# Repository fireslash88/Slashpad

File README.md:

## Slashpad

This is my submission for the Hackpad challenge!

Slashpad is a 6 key macropad with a Rotary Encoder and OLED Display, and uses the QMK Firmware!

--- 
### Inspiration for the name of the pad

I named the pad after my username online! As you can see, my name on github is "fireslash88" and that's pretty much the same for every other account I have online!
I have another username that I actually use more than this one but I prefer to use slash now..

---
### BOM
- 1x Seeed XIAO RP2040
- 6x Cherry MX Switches
- 6x Keycaps
- 1x EC11 Rotary Encoder
- 1x 0.91 inch OLED display
- 7x through-hole 1N4148 Diodes
- 4x M3x16mm screws
- 1x 3D Printed Case
---
### PCB
This is the PCB I created for the Multipad!

This is the schematic that I created using KiCad 10.0!

This is the PCB!

---
### Case
This is the case I modeled in Fusion 360!

---
### Firmware

The Slashpad uses the QMK firmware for everything!
(Will include VIA in the future) 

---
### Thanks!

A great thanks to Hack Club to have made this project possible!

---

### Cats
Yes. I love cats so I decided to put some silly cats I found on Pinterest on the PCB. They're pretty and I love them so uhh... Yeah... Cats.. Meow..

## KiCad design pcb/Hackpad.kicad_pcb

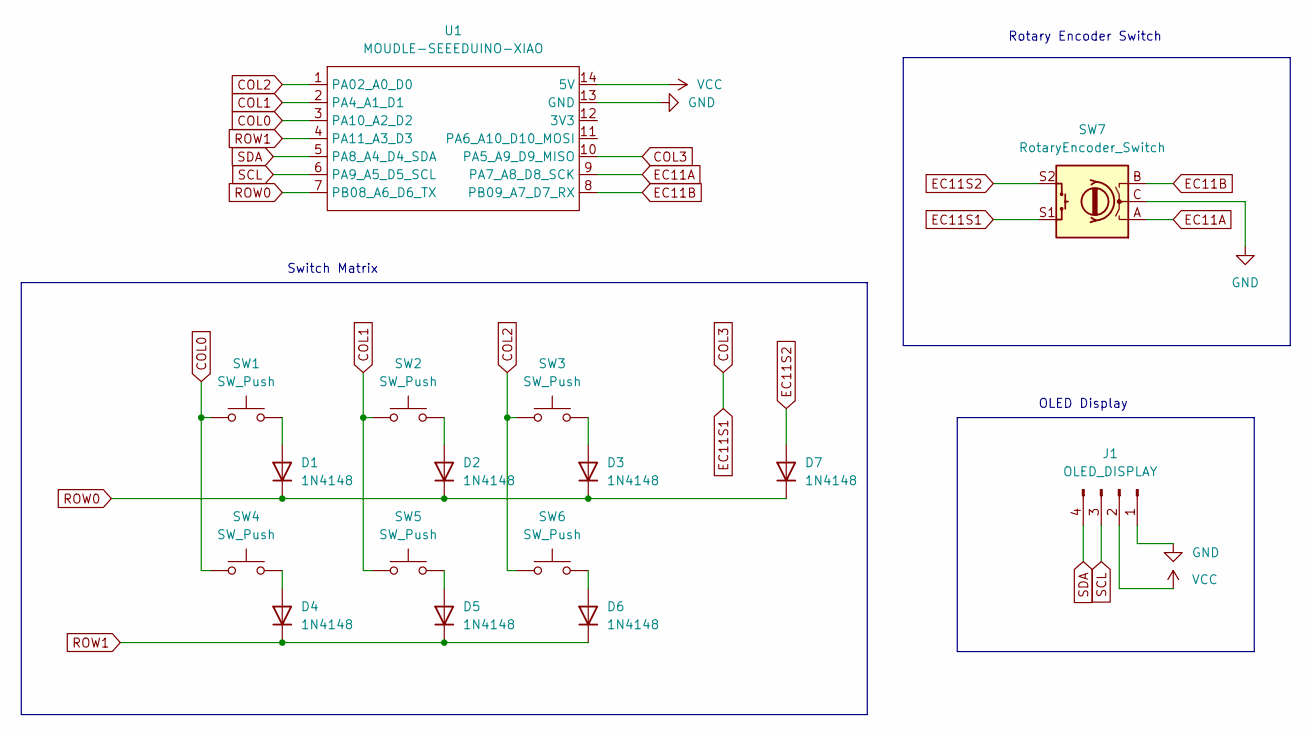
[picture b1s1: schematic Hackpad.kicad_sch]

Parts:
D1, D2, D3, D4, D5, D6, D7: 1N4148; D_DO-35_SOD27_P7.62mm_Horizontal
J1: OLED_DISPLAY; SSD1306-0.91-OLED-4pin-128x32
SW1, SW2, SW3, SW4, SW5, SW6: SW_Push; SW_Cherry_MX_1.00u_PCB
SW7: RotaryEncoder_Switch; RotaryEncoder_Alps_EC11E-Switch_Vertical_H20mm
U1: MOUDLE-SEEEDUINO-XIAO; XIAO-Generic-Hybrid-14P-2.54-21X17.8MM

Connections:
COL0: SW1.1, SW4.1, U1.3 (PA10_A2_D2)
COL1: SW2.1, SW5.1, U1.2 (PA4_A1_D1)
COL2: SW3.1, SW6.1, U1.1 (PA02_A0_D0)
COL3: SW7.S1, U1.10 (PA5_A9_D9_MISO)
EC11A: SW7.A, U1.9 (PA7_A8_D8_SCK)
EC11B: SW7.B, U1.8 (PB09_A7_D7_RX)
EC11S2: D7.2 (A), SW7.S2
GND: J1.1, SW7.C, U1.13 (GND)
unnamed: D1.2 (A), SW1.2
unnamed: D2.2 (A), SW2.2
unnamed: D3.2 (A), SW3.2
unnamed: D4.2 (A), SW4.2
unnamed: D5.2 (A), SW5.2
unnamed: D6.2 (A), SW6.2
ROW0: D1.1 (K), D2.1 (K), D3.1 (K), D7.1 (K), U1.7 (PB08_A6_D6_TX)
ROW1: D4.1 (K), D5.1 (K), D6.1 (K), U1.4 (PA11_A3_D3)
SCL: J1.3, U1.6 (PA9_A5_D5_SCL)
SDA: J1.4, U1.5 (PA8_A4_D4_SDA)
VCC: J1.2, U1.14 (5V)

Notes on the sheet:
OLED Display
Rotary Encoder Switch
Switch Matrix

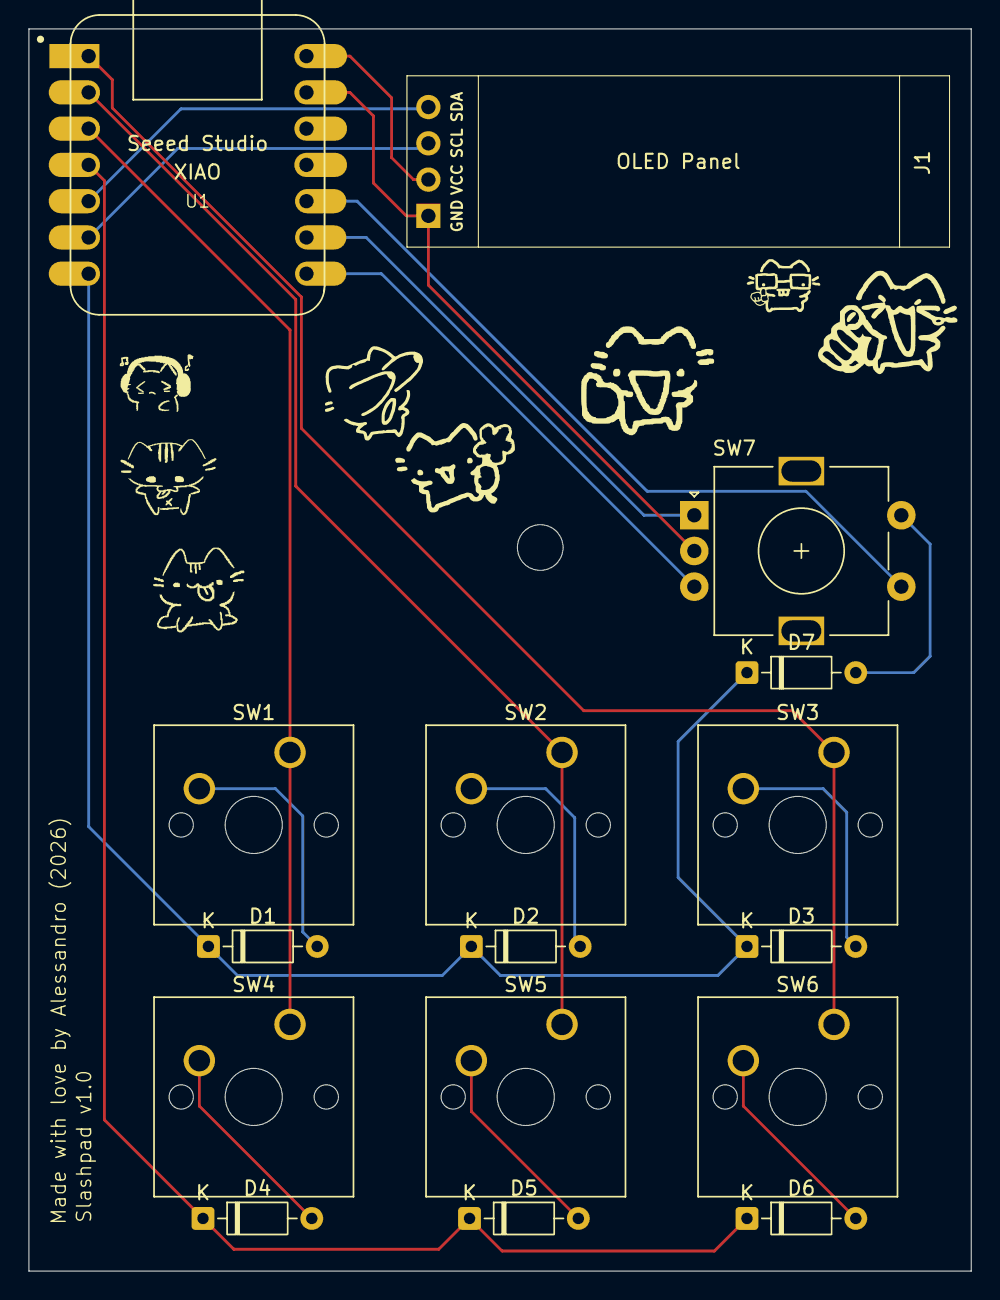
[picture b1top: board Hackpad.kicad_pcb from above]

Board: 2 copper layers, 66.0 x 87.0 mm, 16 parts (0 on the bottom side), 19 nets.

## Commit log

2026-06-09 First commit!
    #1 First commit of the Slashpad!
    -Structured all the files
    -Created the schematic and the PCB itself
    -Started writing the README.md
2026-06-11 Fixes + Adding new files
    - Added new cats on the PCB
    - Adjusted the PCB and routed everything again
    - Adjusted the schematic
2026-06-11 Fixes and new files added
    - Added .step files of the case
    - Added .step file of the whole macropad
    - Added the firmware
    - Modified the readme.md
2026-06-11 Quick fix of the readme.md
2026-06-11 Another quick fix..
